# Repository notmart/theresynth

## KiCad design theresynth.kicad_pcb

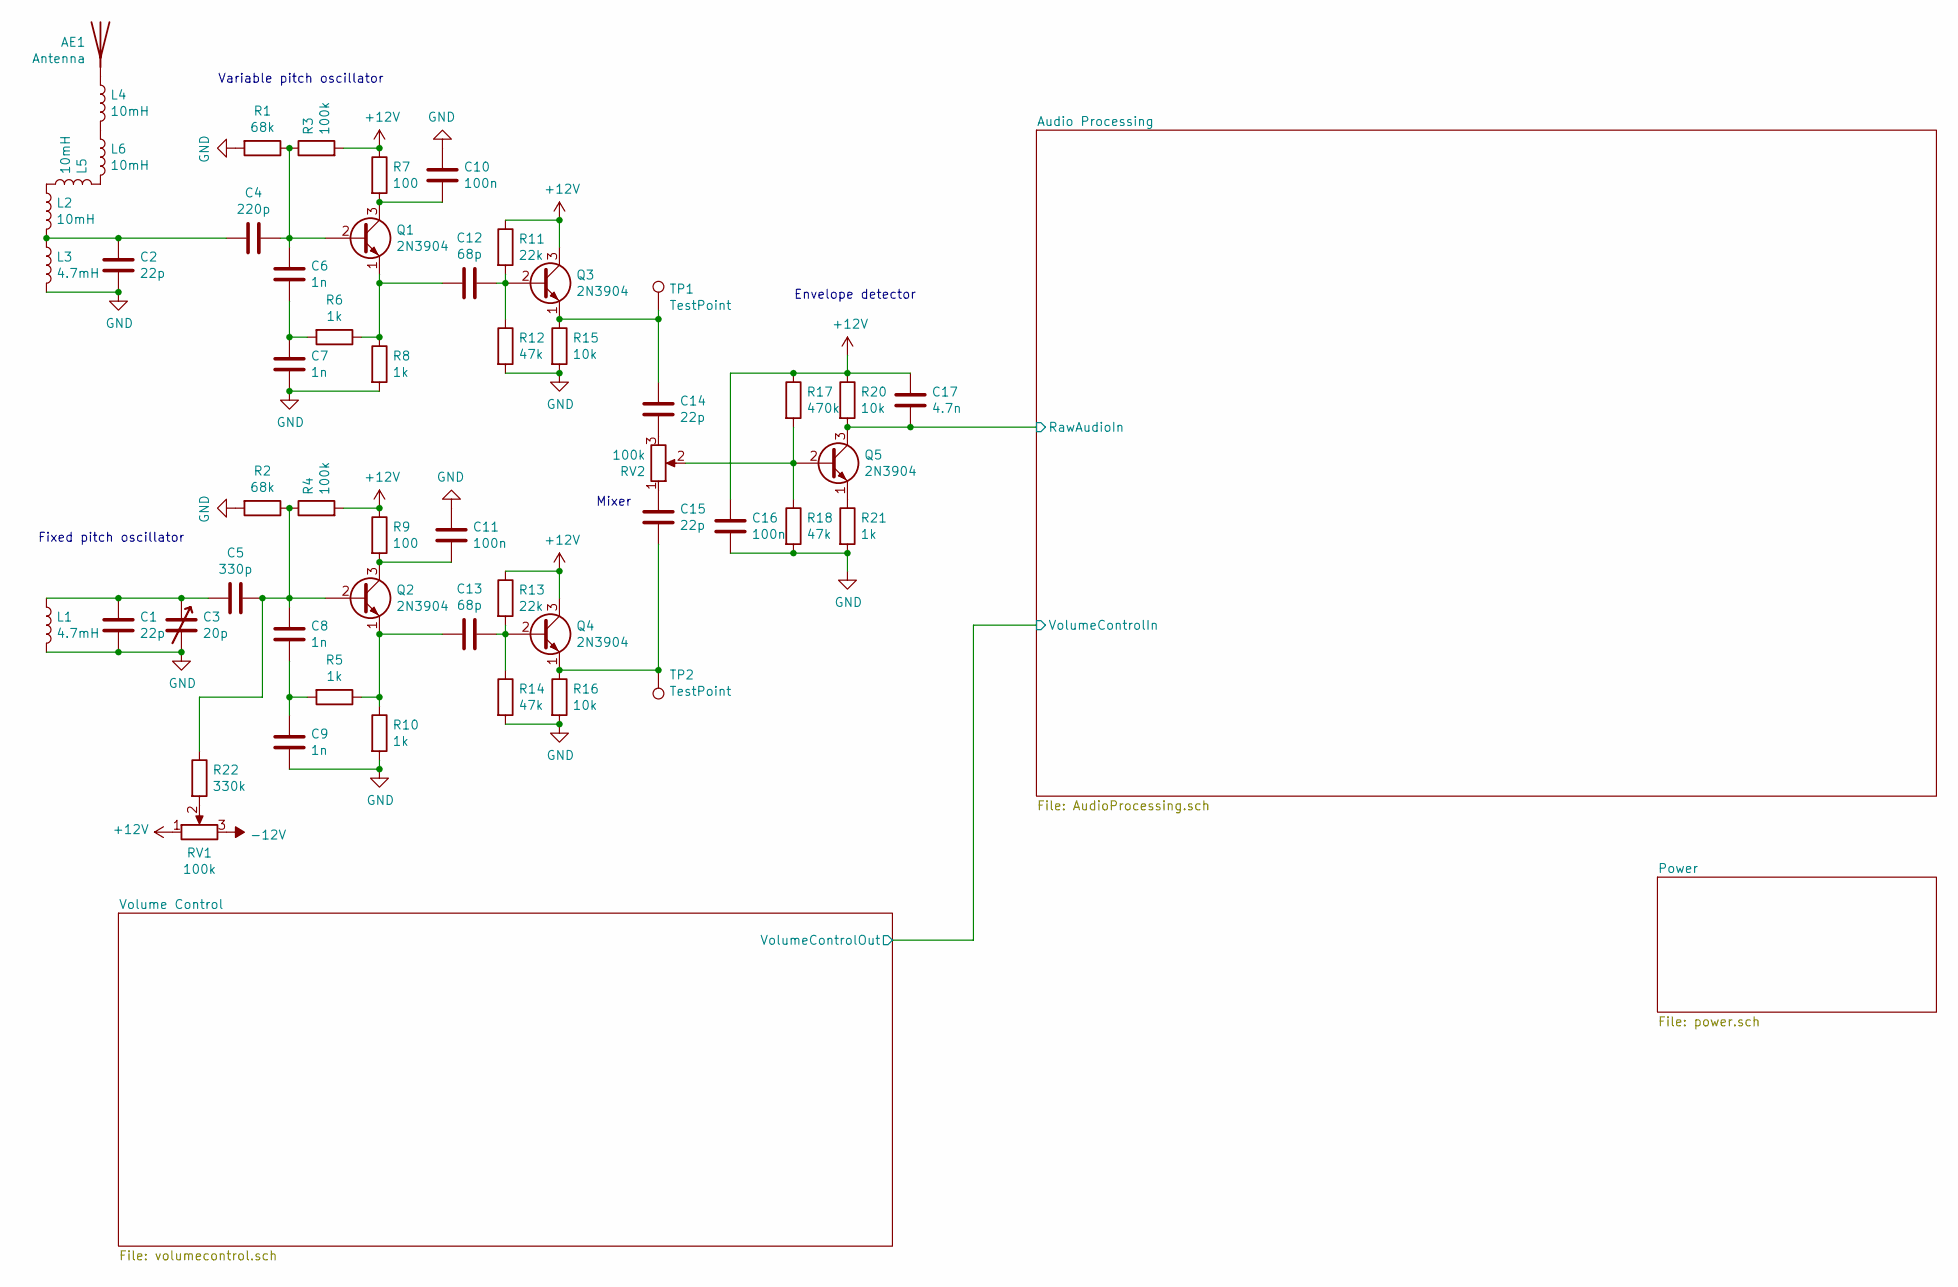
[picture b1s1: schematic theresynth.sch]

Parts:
AE1: Antenna; Connector_F
C1, C2, C14, C15: 22p; C_Disc_D6.0mm_W2.5mm_P5.00mm
C3: 20p; Variable_Capacitor_W6.5mm_P5.00mm
C4: 220p; C_Disc_D6.0mm_W2.5mm_P5.00mm
C5: 330p; C_Disc_D6.0mm_W2.5mm_P5.00mm
C6, C7, C8, C9: 1n; C_Rect_L7.2mm_W2.5mm_P5.00mm_FKS2_FKP2_MKS2_MKP2
C10, C11, C16: 100n; C_Rect_L7.2mm_W2.5mm_P5.00mm_FKS2_FKP2_MKS2_MKP2
C12, C13: 68p; C_Disc_D6.0mm_W2.5mm_P5.00mm
C17: 4.7n; C_Rect_L7.2mm_W2.5mm_P5.00mm_FKS2_FKP2_MKS2_MKP2
L1, L3: 4.7mH; L_Axial_L12.0mm_D5.0mm_P15.24mm_Horizontal_Fastron_MISC
L2, L4, L5, L6: 10mH; L_Radial_D12.5mm_P7.00mm_Fastron_09HCP
Q1, Q2, Q3, Q4, Q5: 2N3904; TO-92_Inline_Wide
R1, R2: 68k; R_Axial_DIN0204_L3.6mm_D1.6mm_P7.62mm_Horizontal
R3, R4: 100k; R_Axial_DIN0204_L3.6mm_D1.6mm_P7.62mm_Horizontal
R5, R6, R8, R10, R21: 1k; R_Axial_DIN0204_L3.6mm_D1.6mm_P7.62mm_Horizontal
R7, R9: 100; R_Axial_DIN0204_L3.6mm_D1.6mm_P7.62mm_Horizontal
R11, R13: 22k; R_Axial_DIN0204_L3.6mm_D1.6mm_P7.62mm_Horizontal
R12, R14, R18: 47k; R_Axial_DIN0204_L3.6mm_D1.6mm_P7.62mm_Horizontal
R15, R16, R20: 10k; R_Axial_DIN0204_L3.6mm_D1.6mm_P7.62mm_Horizontal
R17: 470k; R_Axial_DIN0204_L3.6mm_D1.6mm_P7.62mm_Horizontal
R22: 330k; R_Axial_DIN0204_L3.6mm_D1.6mm_P7.62mm_Horizontal
RV1, RV2: 100k; Potentiometer_Alps_RK163_Single_Horizontal
TP1, TP2: TestPoint; TestPoint_THTPad_1.0x1.0mm_Drill0.5mm

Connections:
+12V: C16.1, C17.1, Q3.3 (C), Q4.3 (C), R3.2, R4.2, R7.1, R9.1, R11.1, R13.1, R17.1, R20.1, RV1.1; also elsewhere on the board
-12V: RV1.3; also elsewhere on the board
/Audio Processing/RawAudioIn: C17.2, Q5.3 (C), R20.2; also elsewhere on the board
GND: C1.2, C2.2, C3.2, C7.2, C9.2, C10.1, C11.1, C16.2, L1.2, L3.2, R1.2, R2.2, R8.2, R10.2, R12.2, R14.2, R15.2, R16.2, R18.2, R21.2; also elsewhere on the board
unnamed: AE1.1, L4.1
unnamed: C1.1, C3.1, C5.2, L1.1
unnamed: C2.1, C4.1, L2.2, L3.1
unnamed: C4.2, C6.1, Q1.2 (B), R1.1, R3.1
unnamed: C5.1, C8.1, Q2.2 (B), R2.1, R4.1, R22.1
unnamed: C6.2, C7.1, R6.2
unnamed: C8.2, C9.1, R5.2
unnamed: C10.2, Q1.3 (C), R7.2
unnamed: C11.2, Q2.3 (C), R9.2
unnamed: C12.1, Q3.2 (B), R11.2, R12.1
unnamed: C12.2, Q1.1 (E), R6.1, R8.1
unnamed: C13.1, Q4.2 (B), R13.2, R14.1
unnamed: C13.2, Q2.1 (E), R5.1, R10.1
unnamed: C14.1, Q3.1 (E), R15.1, TP1.1
unnamed: C14.2, RV2.3
unnamed: C15.1, RV2.1
unnamed: C15.2, Q4.1 (E), R16.1, TP2.1
unnamed: L2.1, L5.2
unnamed: L4.2, L6.1
unnamed: L5.1, L6.2
unnamed: Q5.1 (E), R21.1
unnamed: Q5.2 (B), R17.2, R18.1, RV2.2
unnamed: R22.2, RV1.2

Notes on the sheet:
Variable pitch oscillator
Fixed pitch oscillator
Envelope detector
Mixer

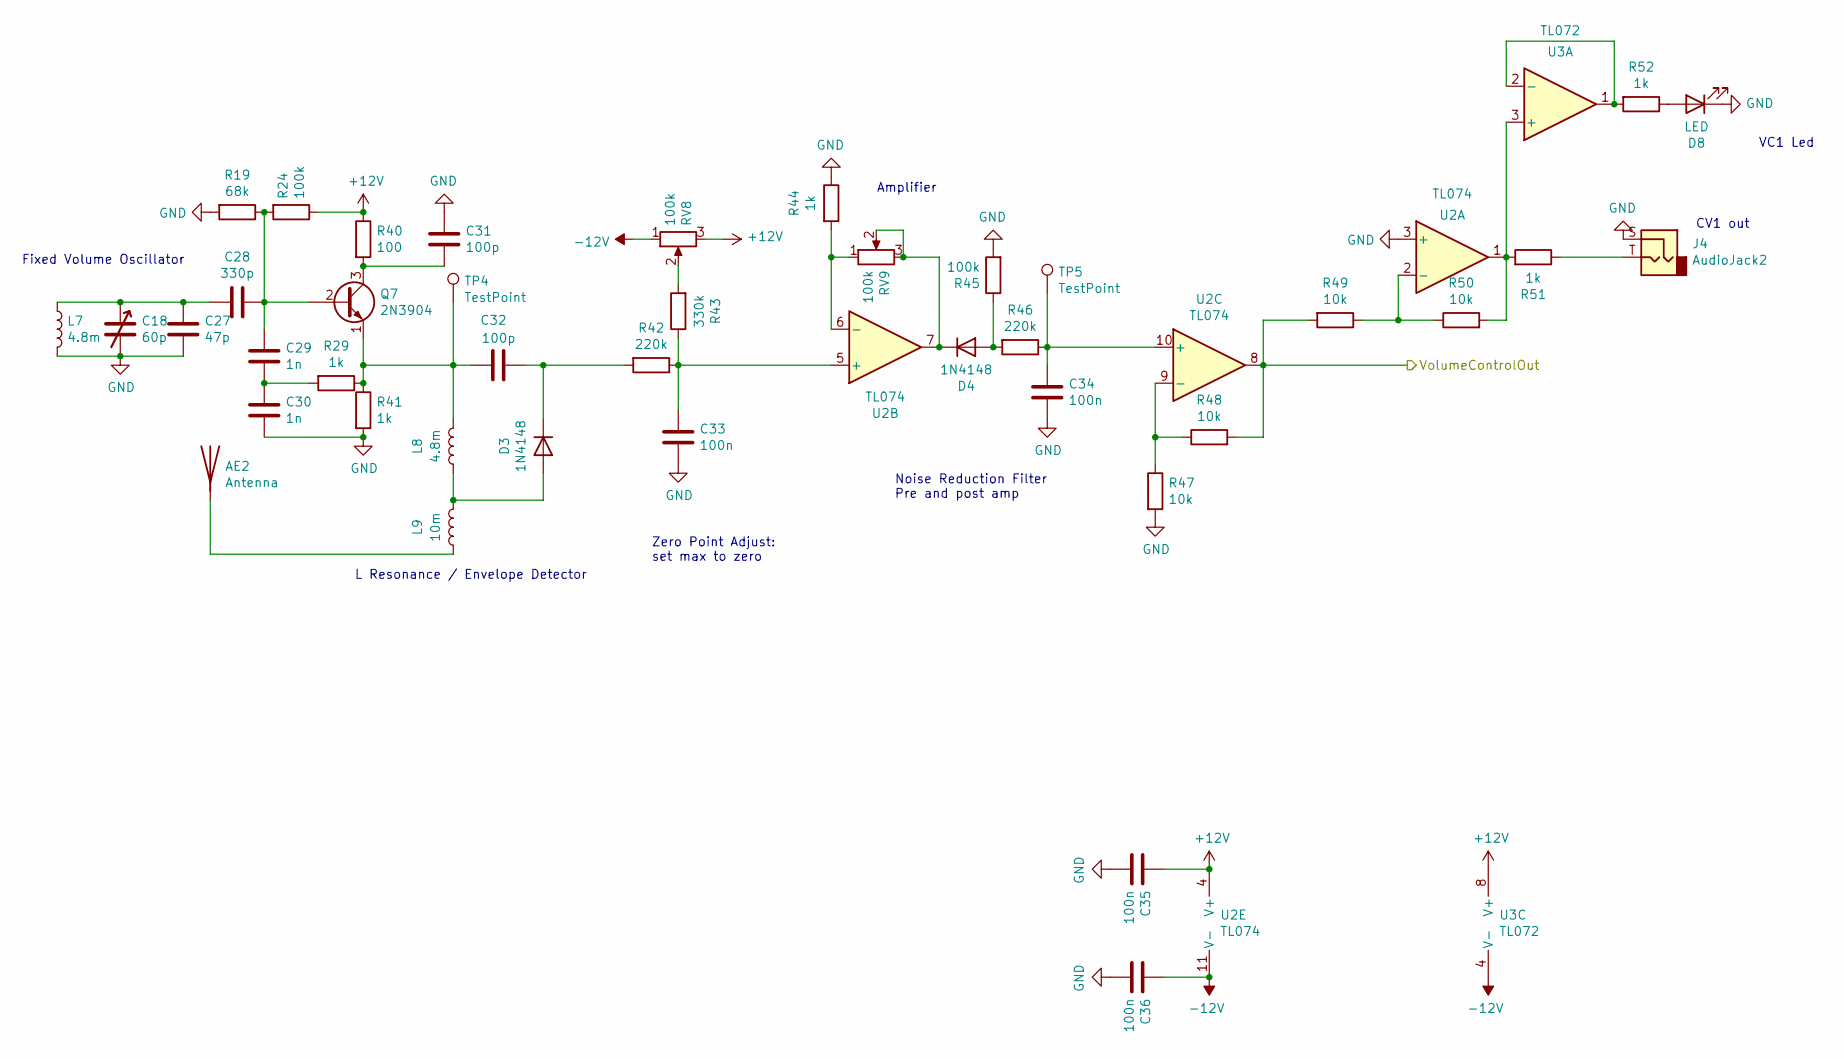
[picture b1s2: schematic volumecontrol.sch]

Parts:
AE2: Antenna; Connector_F
C18: 60p; Variable_Capacitor_W6.5mm_P5.00mm
C27: 47p; C_Disc_D6.0mm_W2.5mm_P5.00mm
C28: 330p; C_Disc_D6.0mm_W2.5mm_P5.00mm
C29, C30: 1n; C_Rect_L7.2mm_W2.5mm_P5.00mm_FKS2_FKP2_MKS2_MKP2
C31: 100p; C_Rect_L7.2mm_W2.5mm_P5.00mm_FKS2_FKP2_MKS2_MKP2
C32: 100p; C_Disc_D6.0mm_W2.5mm_P5.00mm
C33, C34, C35, C36: 100n; C_Rect_L7.2mm_W2.5mm_P5.00mm_FKS2_FKP2_MKS2_MKP2
D3, D4: 1N4148; D_DO-34_SOD68_P7.62mm_Horizontal
D8: LED; LED_D3.0mm
J4: AudioJack2; PJ302M
L7, L8: 4.8m; L_Axial_L12.0mm_D5.0mm_P15.24mm_Horizontal_Fastron_MISC
L9: 10m; L_Radial_D12.5mm_P7.00mm_Fastron_09HCP
Q7: 2N3904; TO-92_Inline_Wide
R19: 68k; R_Axial_DIN0204_L3.6mm_D1.6mm_P7.62mm_Horizontal
R24, R45: 100k; R_Axial_DIN0204_L3.6mm_D1.6mm_P7.62mm_Horizontal
R29, R41, R44, R51, R52: 1k; R_Axial_DIN0204_L3.6mm_D1.6mm_P7.62mm_Horizontal
R40: 100; R_Axial_DIN0204_L3.6mm_D1.6mm_P7.62mm_Horizontal
R42, R46: 220k; R_Axial_DIN0204_L3.6mm_D1.6mm_P7.62mm_Horizontal
R43: 330k; R_Axial_DIN0204_L3.6mm_D1.6mm_P7.62mm_Horizontal
R47, R48, R49, R50: 10k; R_Axial_DIN0204_L3.6mm_D1.6mm_P7.62mm_Horizontal
RV8: 100k; Potentiometer_Bourns_3296W_Vertical
RV9: 100k; Potentiometer_Bourns_3386P_Vertical
TP4, TP5: TestPoint; TestPoint_THTPad_1.0x1.0mm_Drill0.5mm
U2: TL074; DIP-14_W7.62mm_LongPads
U3: TL072; DIP-8_W7.62mm_LongPads

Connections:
+12V: C35.1, R24.1, R40.1, RV8.3, U2.4 (V+), U3.8 (V+); also elsewhere on the board
-12V: C36.1, RV8.1, U2.11 (V-), U3.4 (V-); also elsewhere on the board
/Audio Processing/VolumeControlIn: R48.2, R49.2, U2.8; also elsewhere on the board
GND: C18.2, C27.2, C30.2, C31.1, C33.2, C34.2, C35.2, C36.2, D8.1 (K), J4.S, L7.2, R19.2, R41.2, R44.1, R45.2, R47.2, U2.3 (+); also elsewhere on the board
unnamed: AE2.1, L9.1
unnamed: C18.1, C27.1, C28.2, L7.1
unnamed: C28.1, C29.1, Q7.2 (B), R19.1, R24.2
unnamed: C29.2, C30.1, R29.2
unnamed: C31.2, Q7.3 (C), R40.2
unnamed: C32.1, L8.2, Q7.1 (E), R29.1, R41.1, TP4.1
unnamed: C32.2, D3.1 (K), R42.2
unnamed: C33.1, R42.1, R43.1, U2.5 (+)
unnamed: C34.1, R46.1, TP5.1, U2.10 (+)
unnamed: D3.2 (A), L8.1, L9.2
unnamed: D4.1 (K), RV9.2, RV9.3, U2.7
unnamed: D4.2 (A), R45.1, R46.2
unnamed: D8.2 (A), R52.1
unnamed: J4.T, R51.1
unnamed: R43.2, RV8.2
unnamed: R44.2, RV9.1, U2.6 (-)
unnamed: R47.1, R48.1, U2.9 (-)
unnamed: R49.1, R50.1, U2.2 (-)
unnamed: R50.2, R51.2, U2.1, U3.3 (+)
unnamed: R52.2, U3.1, U3.2 (-)

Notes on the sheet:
Fixed Volume Oscillator
L Resonance / Envelope Detector
Zero Point Adjust: set max to zero
Amplifier
Noise Reduction Filter Pre and post amp
VC1 Led
CV1 out

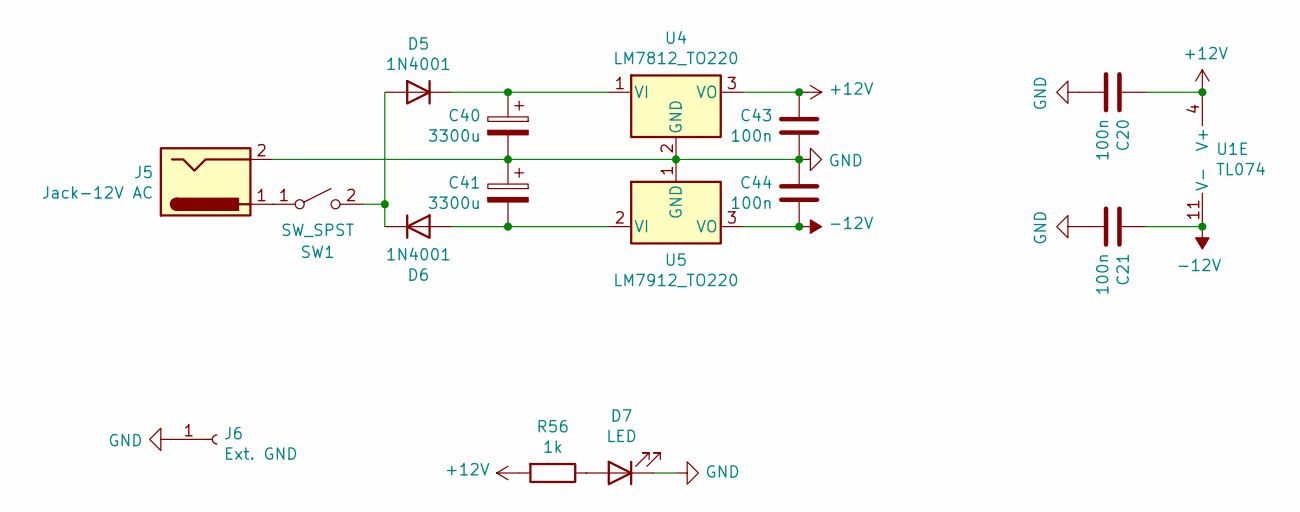
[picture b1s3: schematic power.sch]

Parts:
C20, C21, C43, C44: 100n; C_Rect_L7.2mm_W2.5mm_P5.00mm_FKS2_FKP2_MKS2_MKP2
C40, C41: 3300u; CP_Radial_D13.0mm_P5.00mm
D5, D6: 1N4001; D_DO-35_SOD27_P7.62mm_Horizontal
D7: LED; LED_D3.0mm
J5: Jack-12V AC; BarrelJack_Horizontal
J6: Ext. GND; Pin_D1.4mm_L8.5mm_W2.8mm_FlatFork
R56: 1k; R_Axial_DIN0204_L3.6mm_D1.6mm_P7.62mm_Horizontal
SW1: SW_SPST; Horizontal_SPDT
U1: TL074; DIP-14_W7.62mm_LongPads
U4: LM7812_TO220; TO-220-3_Vertical
U5: LM7912_TO220; TO-220-3_Vertical

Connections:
+12V: C20.1, C43.1, R56.2, U1.4 (V+), U4.3 (VO); also elsewhere on the board
-12V: C21.1, C44.2, U1.11 (V-), U5.3 (VO); also elsewhere on the board
GND: C20.2, C21.2, C40.2, C41.1, C43.2, C44.1, D7.1 (K), J5.2, J6.1, U4.2 (GND), U5.1 (GND); also elsewhere on the board
unnamed: C40.1, D5.1 (K), U4.1 (VI)
unnamed: C41.2, D6.2 (A), U5.2 (VI)
unnamed: D5.2 (A), D6.1 (K), SW1.2 (B)
unnamed: D7.2 (A), R56.1
unnamed: J5.1, SW1.1 (A)

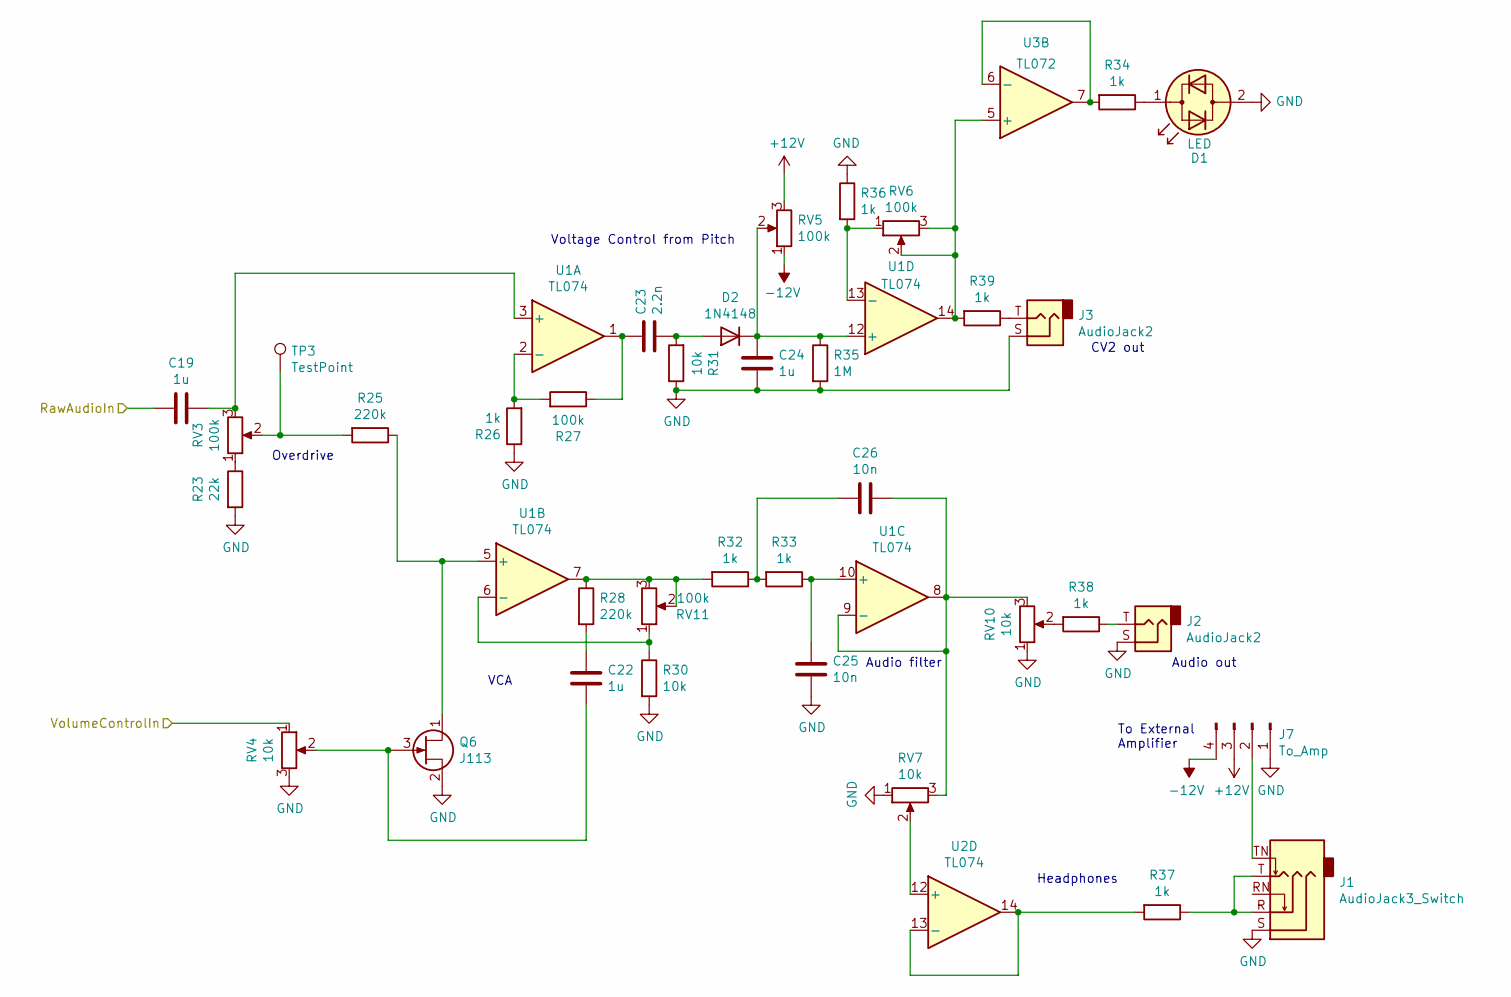
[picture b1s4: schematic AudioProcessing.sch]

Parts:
C19, C22, C24: 1u; C_Rect_L7.0mm_W6.0mm_P5.00mm
C23: 2.2n; C_Rect_L7.2mm_W2.5mm_P5.00mm_FKS2_FKP2_MKS2_MKP2
C25, C26: 10n; C_Rect_L7.2mm_W2.5mm_P5.00mm_FKS2_FKP2_MKS2_MKP2
D1: LED; LED_D3.0mm
D2: 1N4148; D_DO-34_SOD68_P7.62mm_Horizontal
J1: AudioJack3_Switch; Jack_3.5mm_Ledino_KB3SPRS_Horizontal
J2, J3: AudioJack2; PJ302M
J7: To_Amp; PinHeader_1x04_P2.54mm_Vertical
Q6: J113; TO-92_Inline_Wide
R23: 22k; R_Axial_DIN0204_L3.6mm_D1.6mm_P7.62mm_Horizontal
R25, R28: 220k; R_Axial_DIN0204_L3.6mm_D1.6mm_P7.62mm_Horizontal
R26, R32, R33, R34, R36, R37, R38, R39: 1k; R_Axial_DIN0204_L3.6mm_D1.6mm_P7.62mm_Horizontal
R27: 100k; R_Axial_DIN0204_L3.6mm_D1.6mm_P7.62mm_Horizontal
R30, R31: 10k; R_Axial_DIN0204_L3.6mm_D1.6mm_P7.62mm_Horizontal
R35: 1M; R_Axial_DIN0204_L3.6mm_D1.6mm_P7.62mm_Horizontal
RV3: 100k; Potentiometer_Alps_RK163_Single_Horizontal
RV4: 10k; Potentiometer_Bourns_3386P_Vertical
RV5: 100k; Potentiometer_Bourns_3296W_Vertical
RV6, RV11: 100k; Potentiometer_Bourns_3386P_Vertical
RV7, RV10: 10k; Potentiometer_Alps_RK163_Single_Horizontal
TP3: TestPoint; TestPoint_THTPad_1.0x1.0mm_Drill0.5mm
U1, U2: TL074; DIP-14_W7.62mm_LongPads
U3: TL072; DIP-8_W7.62mm_LongPads

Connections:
+12V: J7.3, RV5.3; also elsewhere on the board
-12V: J7.4, RV5.1; also elsewhere on the board
/Audio Processing/RawAudioIn: C19.2; also elsewhere on the board
/Audio Processing/VolumeControlIn: RV4.1; also elsewhere on the board
GND: C24.2, C25.2, D1.2 (AK), J1.S, J2.S, J3.S, J7.1, Q6.2 (S), R23.2, R26.1, R30.2, R31.1, R35.2, R36.1, RV4.3, RV7.1, RV10.1; also elsewhere on the board
unnamed: C19.1, RV3.3, U1.3 (+)
unnamed: C22.1, R28.2
unnamed: C22.2, Q6.3 (G), RV4.2
unnamed: C23.1, D2.2 (A), R31.2
unnamed: C23.2, R27.1, U1.1
unnamed: C24.1, D2.1 (K), R35.1, RV5.2, U1.12 (+)
unnamed: C25.1, R33.1, U1.10 (+)
unnamed: C26.1, RV7.3, RV10.3, U1.8, U1.9 (-)
unnamed: C26.2, R32.1, R33.2
unnamed: D1.1 (KA), R34.1
unnamed: J1.R, J1.T, R37.1
unnamed: J1.TN, J7.2
unnamed: J2.T, R38.1
unnamed: J3.T, R39.1
unnamed: Q6.1 (D), R25.1, U1.5 (+)
unnamed: R23.1, RV3.1
unnamed: R25.2, RV3.2, TP3.1
unnamed: R26.2, R27.2, U1.2 (-)
unnamed: R28.1, R32.2, RV11.2, RV11.3, U1.7
unnamed: R30.1, RV11.1, U1.6 (-)
unnamed: R34.2, U3.6 (-), U3.7
unnamed: R36.2, RV6.1, U1.13 (-)
unnamed: R37.2, U2.13 (-), U2.14
unnamed: R38.2, RV10.2
unnamed: R39.2, RV6.2, RV6.3, U1.14, U3.5 (+)
unnamed: RV7.2, U2.12 (+)

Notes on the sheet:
VCA
Overdrive
Audio filter
Audio out
Voltage Control from Pitch
CV2 out
Headphones
To External Amplifier

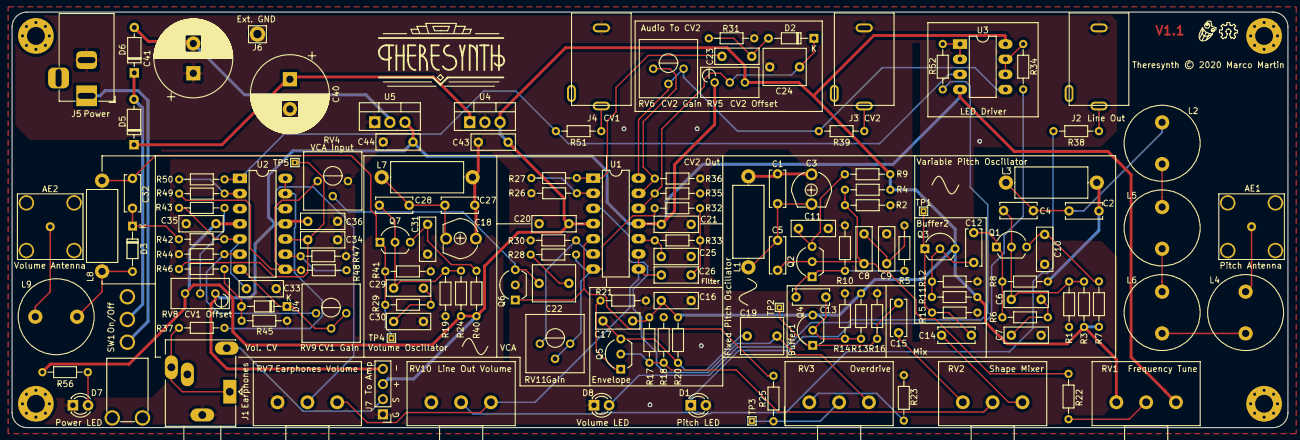
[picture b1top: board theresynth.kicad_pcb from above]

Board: 2 copper layers, 214.0 x 69.7 mm, 148 parts (0 on the bottom side), 79 nets.

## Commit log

2020-09-17 completely connected
2020-09-22 add phones output
2020-10-07 removed 2 opamp units
2020-10-12 full connection before relayouting labels
2020-10-16 migrate audio processing to new sheet
2020-10-27 1.0 for fabrication
2021-06-01 add panels
2021-12-06 add gerber
2021-12-06 add license

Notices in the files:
theresynth.kicad_pcb:
Theresynth © 2020 Marco Martin
